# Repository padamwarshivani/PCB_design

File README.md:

# PCB_design
Fundamental PCB designs

Basic electronics widely used as a daily essential, practicing PCB circuit design and analysis. Beautifying various factors of electronics.

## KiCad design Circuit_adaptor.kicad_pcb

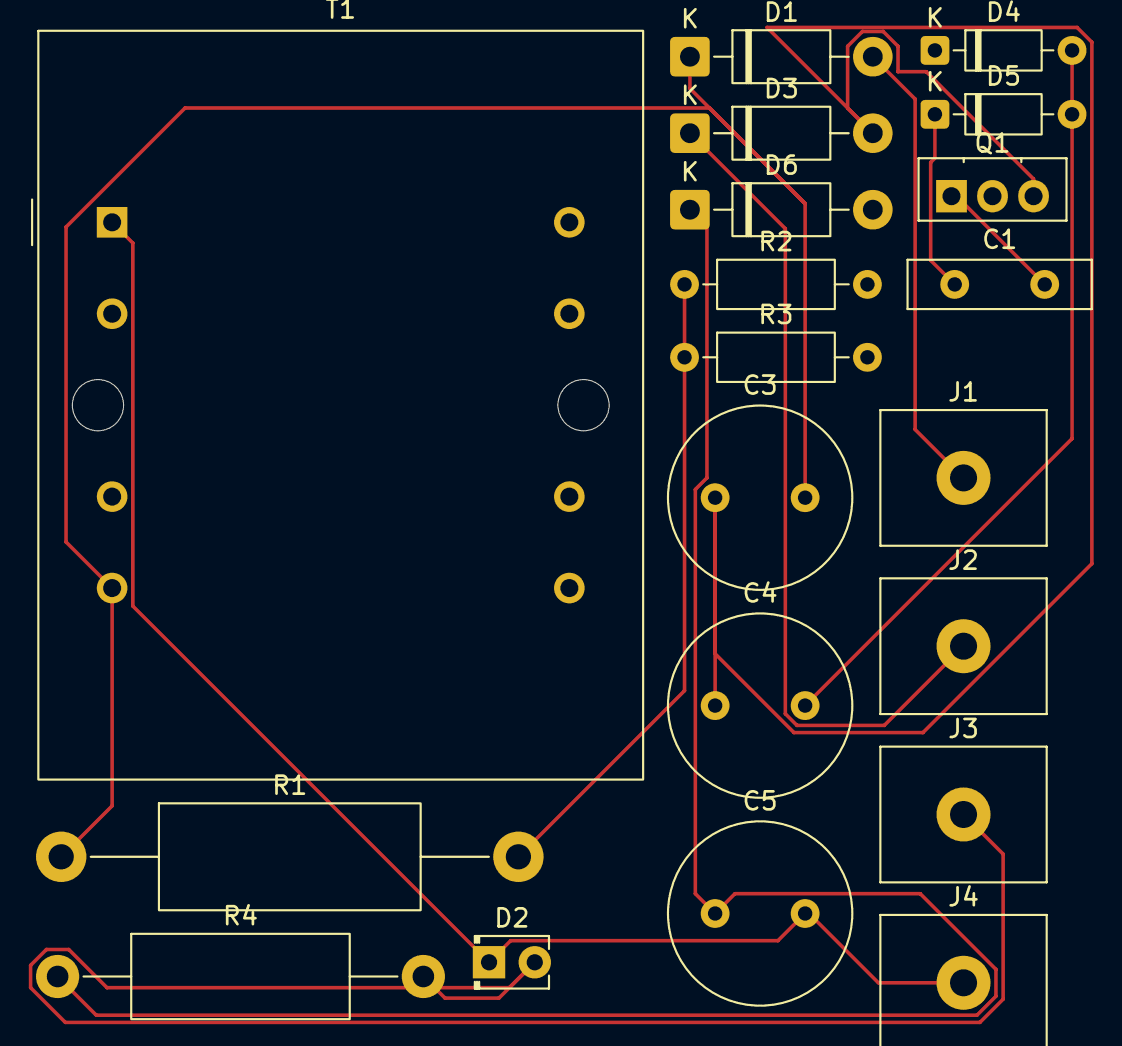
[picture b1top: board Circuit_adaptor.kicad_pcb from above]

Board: 2 copper layers, 20 parts (0 on the bottom side), 10 nets.

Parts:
C1: 1nF; C_Disc_D10.0mm_W2.5mm_P5.00mm
C3: 2u2; C_Radial_D10.0mm_H16.0mm_P5.00mm
C4: 22uf; C_Radial_D10.0mm_H12.5mm_P5.00mm
C5: 470uF; C_Radial_D10.0mm_H16.0mm_P5.00mm
D1, D3: 1N4007; D_DO-41_SOD81_P10.16mm_Horizontal
D2: 3mm; LED_D2.0mm_W4.0mm_H2.8mm_FlatTop
D4: 1N4148; D_DO-35_SOD27_P7.62mm_Horizontal
D5: 6V2; D_DO-35_SOD27_P7.62mm_Horizontal
D6: 1N5819; D_DO-41_SOD81_P10.16mm_Horizontal
J1, J2, J3, J4: Screw_Terminal_01x01; TerminalBlock_MetzConnect_360271_1x01_Horizontal_ScrewM3.0_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
Q1: MJE13003; TO-126-3_Vertical
R1: 1M; R_Axial_DIN0614_L14.3mm_D5.7mm_P25.40mm_Horizontal
R2: 5k; R_Axial_DIN0207_L6.3mm_D2.5mm_P10.16mm_Horizontal
R3: 8k; R_Axial_DIN0207_L6.3mm_D2.5mm_P10.16mm_Horizontal
R4: 1k; R_Axial_DIN0414_L11.9mm_D4.5mm_P20.32mm_Horizontal
T1: Transformer_1P_2S; Transformer_Triad_VPP16-310

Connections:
unnamed: D1.2 (A), J1.1 (Pin_1_1)
unnamed: C3.2, D1.1 (K), R1.1, T1.6 (SD)
unnamed: D2.2 (A), J3.1 (Pin_1_1), R4.2
unnamed: C5.2, D2.1 (K), J4.1 (Pin_1_1), T1.1 (AA)
unnamed: C3.1, C4.1, D3.2 (A), Q1.3 (E), T1.3 (SA)
unnamed: D3.1 (K), J2.1 (Pin_1_1)
unnamed: C4.2, D4.2 (A), D5.2 (A)
unnamed: C1.2, D4.1 (K), Q1.1 (B), R1.2, R2.1, R3.1
unnamed: C1.1, D5.1 (K), R2.2, R3.2, T1.4 (SB)
unnamed: C5.1, D6.1 (K), R4.1
